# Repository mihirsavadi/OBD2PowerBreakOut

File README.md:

# OBD2PowerBreakOut Board

A simple breakout board that uses inputs from an OBD2 pigtail, and breaks them out with a series of XT30PW connectors.
Each power channel is fuse protected with standard automotive fuses, includes an LED to for easy FUSE integrity
checking, and selectability between 'always on' or 'only on after ignition'. The aforementioned selectability is
accomplished by jumping two pins -- this is self-descriptive on the pcb.

The PIN that connects to power only upon ignition differs between brands. This pin is called the ACC pin. You will have
to research and find out which PIN corresponds to your specific ACC pin. You can also use a multimeter to test and find
out. Below is the standard pinout for an OBD2 connector -- the ACC pin can only exist on any one of the vendor specific
pins. For my 2004 Land Rover Discovery II, the ACC pin is located at pin ???.

The color codes in the following pin-out are in reference to the pigtail found here --
https://www.amazon.com/dp/B07F16GPMB?ref=ppx_yo2_dt_b_product_details&th=1 (iKKEGOL 16 Pin J1962 OBD2 OBD-II Male Connector to Open Plug Wire, OBD Diagnostic Extension Cable Pigtail for DIY (60cm 24" inch, 2ft))
1. **Black** Vendor  
2. **Brown** - J1850 Bus+
3. **Red** - Vendor
4. **Orange** - chassis ground
5. **Yellow** - signal ground
6. **Green** - CAN high
7. **Blue** - K-line
8. **Purple** - Vendor
9. **Gray** - Vendor
10. **White-** J1850 BUS
11. **Pink** - Vendor
12. **Teal** - Vendor
13. **Black/White** - Vendor
14. **Brown/White** - CAN low
15. **Red/White** - K line low
16. **Green/White** - Battery

XT30 connectors are used in this board for easy jerry-rigging of accessories -- XT30's are easy to source, easy to
install, and reliable.

I permanently run an UltraGauge to monitor various information in real time, and as such needed more than just 1 OBD2
port in order to run the OBD2_PowerBreakOut board. I simply used a Y splitter like this one --
https://www.amazon.com/gp/product/B07K6MWQTB/ref=ppx_yo_dt_b_search_asin_title?ie=UTF8&psc=1.

Below are some screenshots of the rendering of the assembled board. I will include real-life photos once assembled.

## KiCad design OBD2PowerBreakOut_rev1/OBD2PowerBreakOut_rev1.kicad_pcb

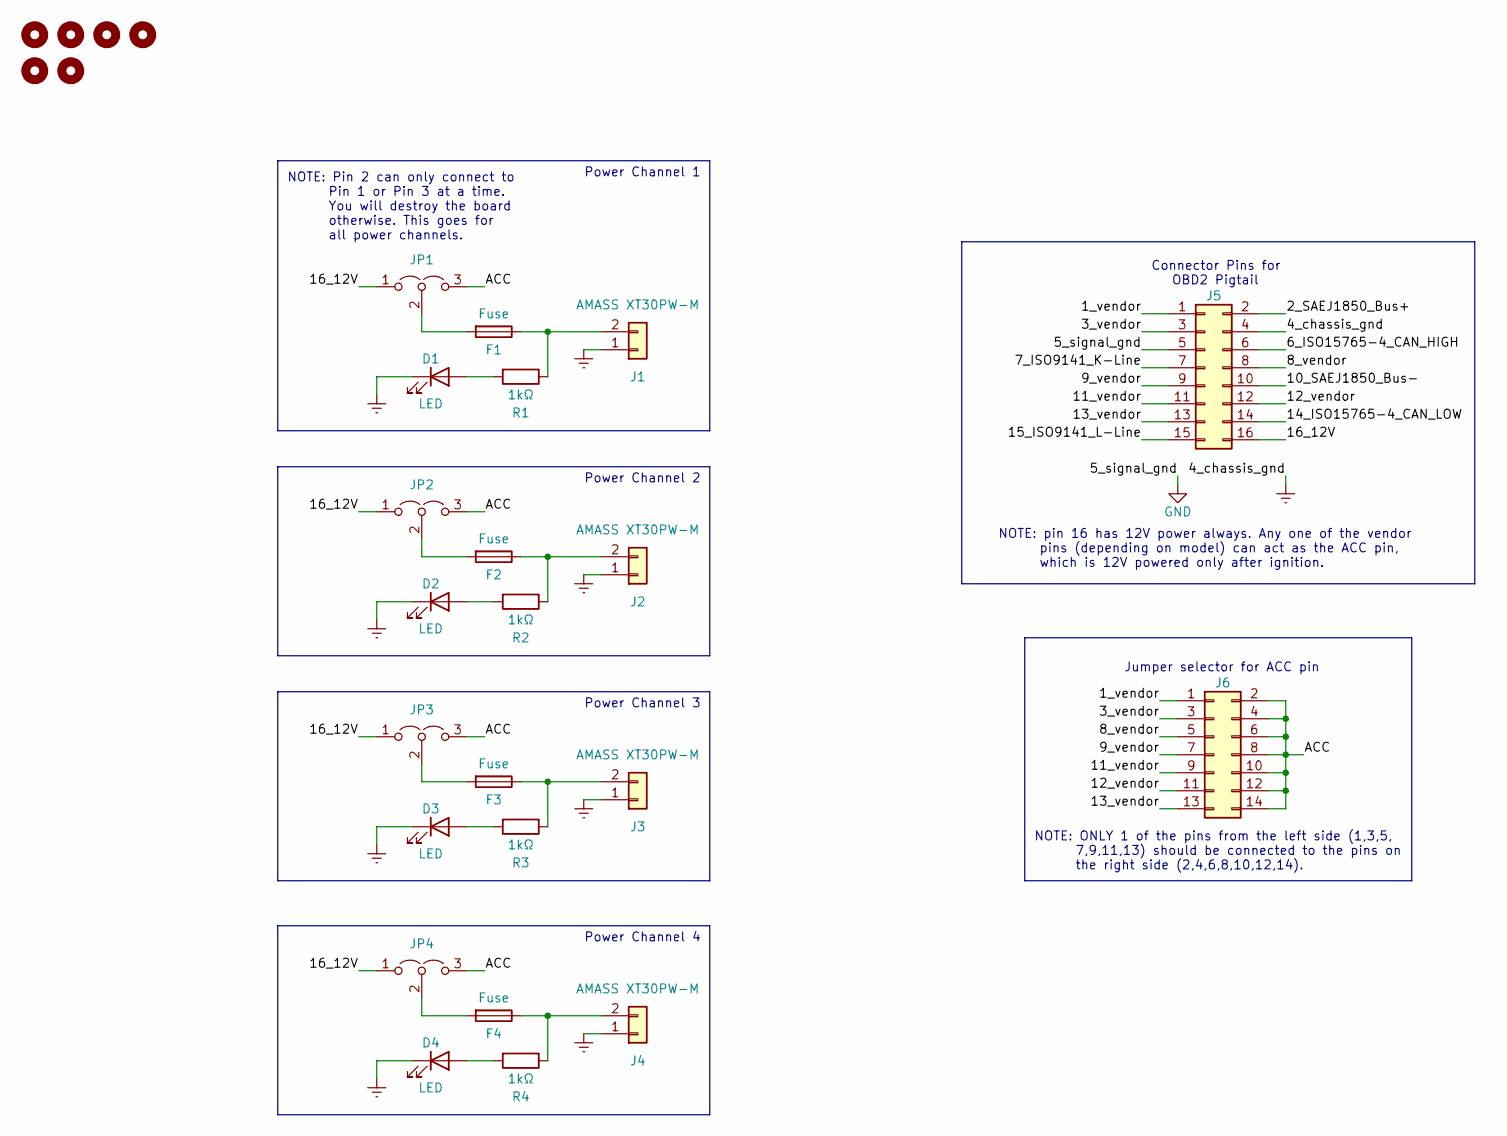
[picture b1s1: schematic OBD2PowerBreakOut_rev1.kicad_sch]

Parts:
D1, D2, D3, D4: LED; LED_0805_2012Metric_Pad1.15x1.40mm_HandSolder
F1, F2, F3, F4: Fuse; FuseHolder_Keystone_3557-2
H1, H3, H5, H6: M3 Mounting Hole; MountingHole_3.2mm_M3
H2, H4: M2 strain relief hole; MountingHole_2.2mm_M2
J1, J2, J3, J4: AMASS XT30PW-M; AMASS_XT30PW-M_1x02_P2.50mm_Horizontal
J5: Conn_02x08_Odd_Even; PinHeader_2x08_P2.54mm_Vertical
J6: Conn_02x07_Odd_Even; PinHeader_2x07_P2.54mm_Vertical
JP1, JP2, JP3, JP4: Jumper_3_Open; PinHeader_1x03_P2.54mm_Vertical
R1, R2, R3, R4: 1kΩ; R_0805_2012Metric_Pad1.20x1.40mm_HandSolder

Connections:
/1_vendor: J5.1, J6.1
/2_SAEJ1850_Bus+: J5.2
/3_vendor: J5.3, J6.3
/6_ISO15765-4_CAN_HIGH: J5.6
/7_ISO9141_K-Line: J5.7
/8_vendor: J5.8, J6.5
/9_vendor: J5.9, J6.7
/10_SAEJ1850_Bus-: J5.10
/11_vendor: J5.11, J6.9
/12_vendor: J5.12, J6.11
/13_vendor: J5.13, J6.13
/14_ISO15765-4_CAN_LOW: J5.14
/15_ISO9141_L-Line: J5.15
/16_12V: J5.16, JP1.1 (A), JP2.1 (A), JP3.1 (A), JP4.1 (A)
/ACC: J6.2, J6.4, J6.6, J6.8, J6.10, J6.12, J6.14, JP1.3 (B), JP2.3 (B), JP3.3 (B), JP4.3 (B)
Earth: D1.1 (K), D2.1 (K), D3.1 (K), D4.1 (K), J1.1, J2.1, J3.1, J4.1, J5.4
GND: J5.5
unnamed: D1.2 (A), R1.2
unnamed: D2.2 (A), R2.2
unnamed: D3.2 (A), R3.2
unnamed: D4.2 (A), R4.2
unnamed: F1.1, J1.2, R1.1
unnamed: F1.2, JP1.2 (C)
unnamed: F2.1, J2.2, R2.1
unnamed: F2.2, JP2.2 (C)
unnamed: F3.1, J3.2, R3.1
unnamed: F3.2, JP3.2 (C)
unnamed: F4.1, J4.2, R4.1
unnamed: F4.2, JP4.2 (C)

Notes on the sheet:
Power Channel 1
Power Channel 3
Jumper selector for ACC pin
Power Channel 2
NOTE: ONLY 1 of the pins from the left side (1,3,5, 7,9,11,13) should be connected to the pins on the right side (2,4,6,8,10,12,14).
Connector Pins for OBD2 Pigtail
NOTE: Pin 2 can only connect to Pin 1 or Pin 3 at a time. You will destroy the board otherwise. This goes for all power channels.
NOTE: pin 16 has 12V power always. Any one of the vendor pins (depending on model) can act as the ACC pin, which is 12V powered only after ignition.
Power Channel 4

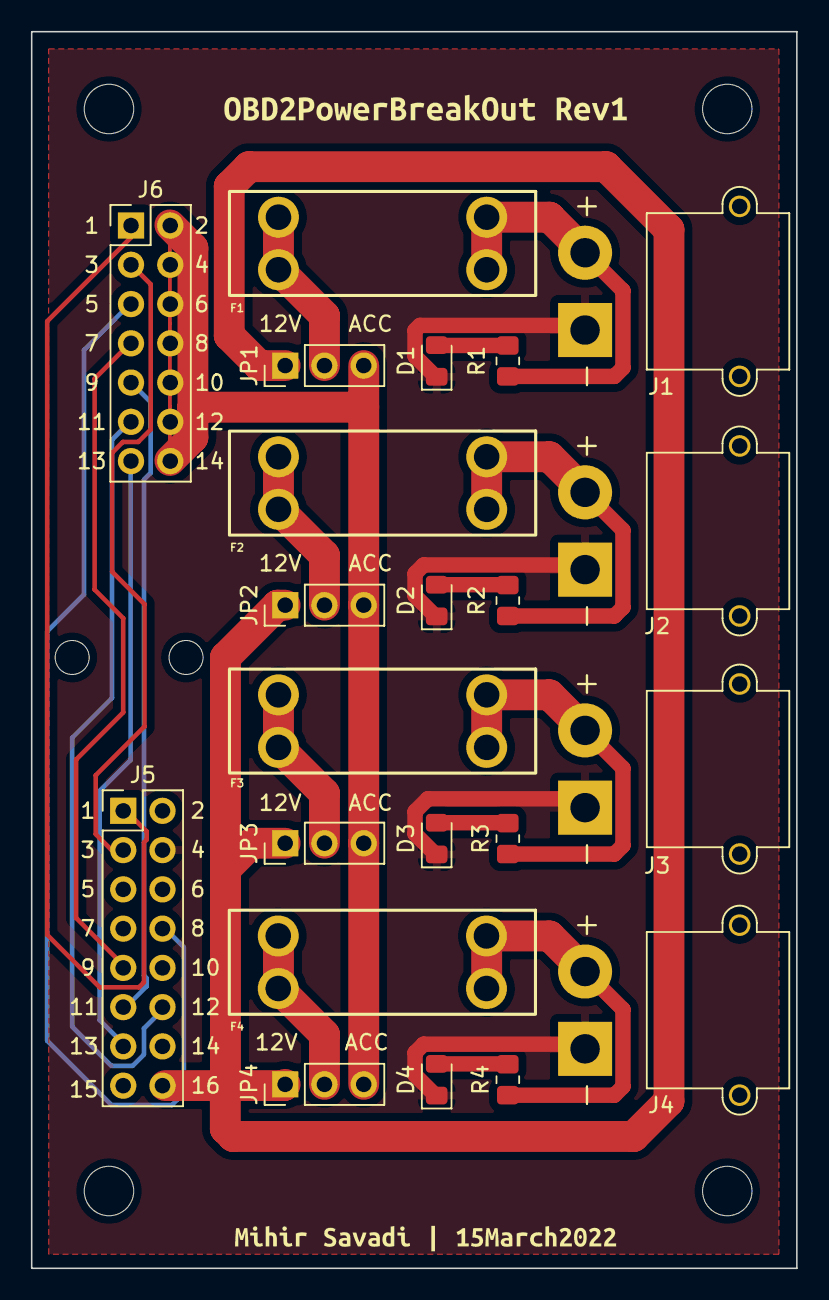
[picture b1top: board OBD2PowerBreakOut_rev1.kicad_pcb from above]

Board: 4 copper layers, 49.5 x 80.0 mm, 30 parts (0 on the bottom side), 22 nets.

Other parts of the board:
kibuzzard-6231480B: G***; kibuzzard-6231480B
kibuzzard-6231482B: G***; kibuzzard-6231482B

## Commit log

2022-03-17 added license
2022-03-17 added schematic

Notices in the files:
README.md:
License: CC BY-NC-SA 4.0
